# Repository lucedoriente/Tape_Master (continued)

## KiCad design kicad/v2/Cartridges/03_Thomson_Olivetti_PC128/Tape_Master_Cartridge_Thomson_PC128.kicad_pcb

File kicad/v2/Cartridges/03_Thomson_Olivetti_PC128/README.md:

# Tape Master v2 — Expansion Cartridge #03
## Thomson MO5 / TO7 / MO6 / TO8 / TO9 & Olivetti Prodest PC 128 Interface

---

### 1. Overview & Supported Systems
This hardware cartridge provides full bidirectional cassette emulation, high-speed acquisition, motor control sensing, and analog soundtrack digitization for the entire family of Thomson 8-bit computers and their international counterparts:
- **Thomson MO Series**: MO5, MO5E, MO5NR, MO6.
- **Thomson TO Series**: TO7, TO7/70, TO8, TO8D, TO9, TO9+.
- **Olivetti Prodest PC 128**: Licensed Italian rebadged version of the Thomson MO6.

The cartridge features:
1. **Universal 40-Pin Right-Angle Bus (`J1`)**: Perfectly coplanar to the Tape Master Mainboard.
2. **Standard 5-Pin DIN 180° Female Socket (`J2`)**: Compatible with original Thomson LEP (*Lecteur Enregistreur de Programmes*) DIN cables.
3. **Bench Test Header (`J3`)**: 6-pin 2.54 mm header in parallel with detailed silkscreen pinout labels for easy logic analyzer, oscilloscope, and bench testing.
4. **Smart Auto-ID EEPROM (`U1`)**: 24C02 on I2C bus identifying Cartridge ID `#03`.
5. **Bidirectional Signal Conditioning**:
   - `READ` (Cassette In to Computer): Buffered with 74HCT06 open-collector inverter stage with 4.7kΩ pull-up for sharp 5V TTL rise/fall times.
   - `WRITE` (Cassette Out from Computer): Scaled via 2.2kΩ / 3.3kΩ voltage divider and clamped to +3.3V/GND via high-speed Schottky diode BAT54S (`D1`).
   - `REM` (Motor Remote Control): Pull-up to +5V (10kΩ) and level scaled/clamped via BAT54S (`D2`) to feed RP2040 `MOTOR_SENSE`.
   - `AUDIO` (Soundtrack / Secondary channel): AC-coupled via 4.7µF capacitor `C3` into the auxiliary analog digitizer `AUDIO_RAW_L`.
6. **ESD TVS Array (`D3`)**: USBLC6-2SC6 protecting all externally exposed lines against electrostatic discharge.

---

### 2. Connector Pinouts

#### DIN 5-Pin 180° Female Receptacle (`J2`)
Standard DIN 41524 / IEC 60130-9 socket:

| Pin | Net Name | Function | Direction | Electrical Standard |
| :---: | :---: | :--- | :--- | :--- |
| **1** | `THOMSON_REM` | Motor Remote Control | Host $\rightarrow$ Tape Master | Open-Collector / Relay control |
| **2** | `GND` | Ground & Shield reference | Common Power Reference | 0V |
| **3** | `THOMSON_AUDIO`| Analog Audio Channel | Tape Master $\rightarrow$ Host | Analog Audio ($~1\text{V}_{pp}$) |
| **4** | `THOMSON_READ` | Cassette Data In (EAR) | Tape Master $\rightarrow$ Host | 5V TTL Digital Pulses |
| **5** | `THOMSON_WRITE`| Cassette Data Out (MIC)| Host $\rightarrow$ Tape Master | 5V TTL Digital Square Waves |

#### Bench Test Pin-Header (`J3`)
6-pin 2.54 mm right-angle pin-header:

| Pin | Net Name | Description |
| :---: | :---: | :--- |
| **1** | `GND` | Ground reference |
| **2** | `+5V` | Tape Master System +5V Supply |
| **3** | `THOMSON_REM` | Motor Remote Control Sense line |
| **4** | `THOMSON_AUDIO`| Analog Audio soundtrack ingest |
| **5** | `THOMSON_READ` | Buffered 5V Cassette Data In to Host |
| **6** | `THOMSON_WRITE`| Scaled Cassette Data Out from Host |

---

### 3. Production Deliverables Summary

| Artifact | File Name | Description |
| :--- | :--- | :--- |
| **Schematic (PDF)** | `Tape_Master_Cartridge_Thomson_PC128.pdf` | Complete single-sheet schematic with standard page settings |
| **Schematic (SVG)** | `Tape_Master_Cartridge_Thomson_PC128_Sch.svg` | Vector schematic graphic |
| **3D CAD Model (STEP)**| `Tape_Master_Cartridge_Thomson_PC128.step` | Full 3D solid mechanical model |
| **PCB Layout (Top PDF)**| `Tape_Master_Cartridge_Thomson_PC128_Top.pdf` | Vector drawing of Top Copper, Silk, Mask & Edge.Cuts |
| **PCB Layout (Bottom PDF)**| `Tape_Master_Cartridge_Thomson_PC128_Bottom.pdf` | Vector drawing of Bottom Copper, Silk, Mask & Edge.Cuts |
| **PCB Layout (Top SVG)**| `Tape_Master_Cartridge_Thomson_PC128_Top.svg` | Vector layout graphic |
| **Gerber & Drill Files** | `gerbers/` (26 files) | Standard RS-274X Gerbers and Excellon drill files |
| **ERC Report** | `Tape_Master_Cartridge_Thomson_PC128-erc.rpt` | **0 Violations / 0 Warnings** |
| **DRC Report** | `Tape_Master_Cartridge_Thomson_PC128-drc.rpt` | **0 Violations / 0 Unconnected / 0 Parity Issues** |

---

### 4. Verification & Validation Gate
- **KiCad 9.0 CLI ERC**: Passed with **0 errors, 0 warnings**.
- **KiCad 9.0 CLI DRC**: Passed with **0 violations, 0 unconnected items, 0 schematic parity issues**.
- **Compliance Rules**:
  - Mechanical profile $74.00\text{ mm} \times 55.00\text{ mm}$ with $6.00\text{ mm} \times 8.00\text{ mm}$ retention cutouts on `Edge.Cuts`.
  - Zero redundant activity LEDs on cartridge; full UI diagnostics central on Daughterboard.
  - Cartouche with Alessio Iodice, CC BY-NC-SA 4.0 license, and `© 2026 by Alessio Iodice` silkscreen copyright.

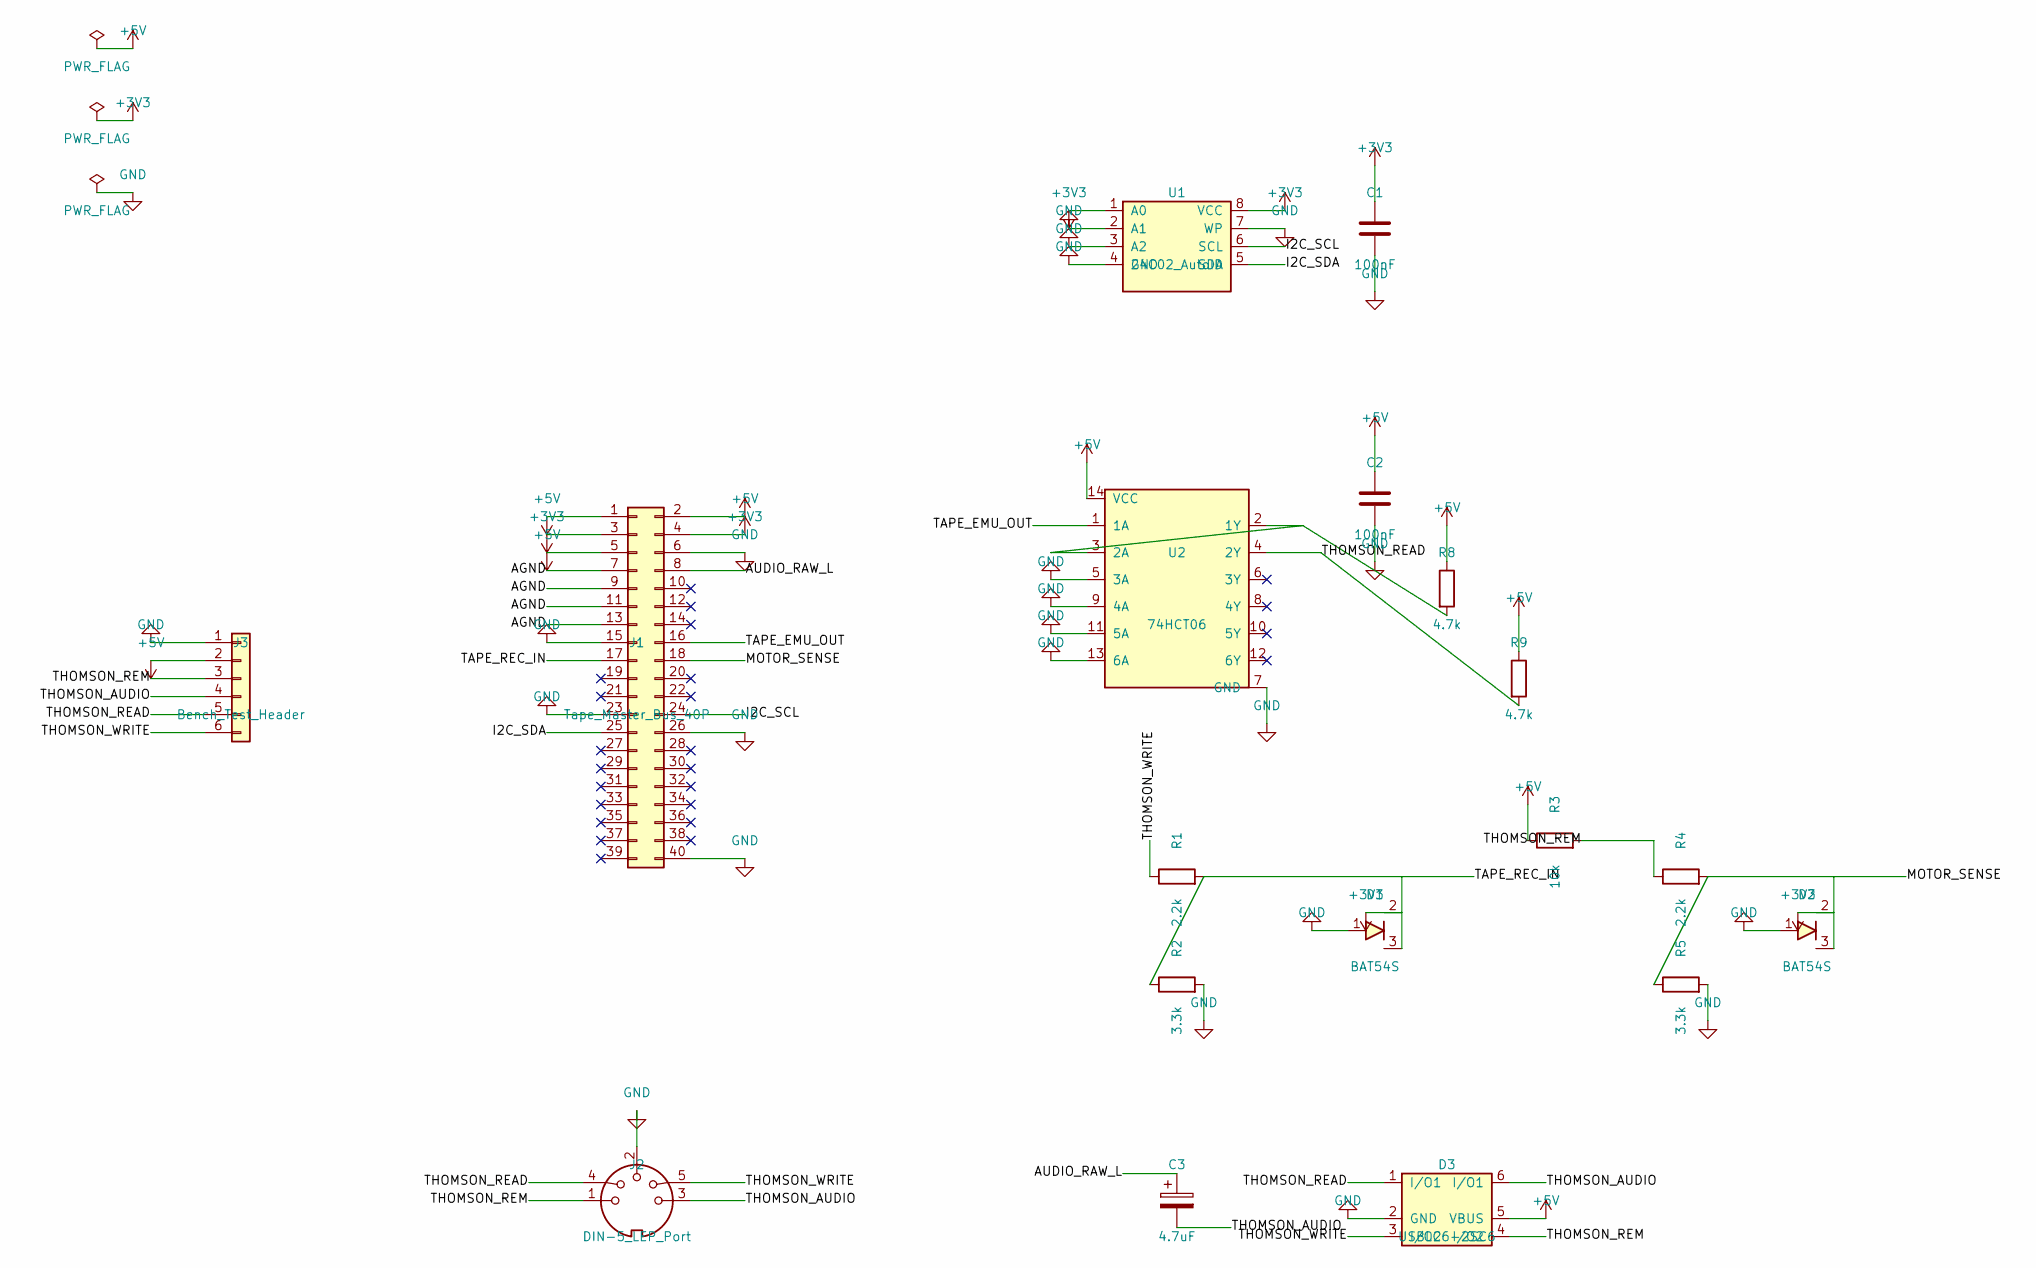
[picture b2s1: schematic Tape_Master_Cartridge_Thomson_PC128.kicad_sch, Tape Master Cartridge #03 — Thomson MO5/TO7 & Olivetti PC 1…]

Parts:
C1, C2: 100nF; C_0805_2012Metric
C3: 4.7uF; CP_Elec_5x5.4
D1, D2: BAT54S; SOT-23
D3: USBLC6-2SC6; SOT-23-6
J1: Tape_Master_Bus_40P; PinSocket_2x20_P2.54mm_Horizontal_Cartridge
J2: DIN-5_LEP_Port; DIN-5_180_Horizontal_CUI_SDS-50J
J3: Bench_Test_Header; PinHeader_1x06_P2.54mm_Vertical
R1, R4: 2.2k; R_0805_2012Metric
R2, R5: 3.3k; R_0805_2012Metric
R3: 10k; R_0805_2012Metric
R8, R9: 4.7k; R_0805_2012Metric
U1: 24C02_AutoID; SOIC-8_3.9x4.9mm_P1.27mm
U2: 74HCT06; SOIC-14_3.9x8.7mm_P1.27mm

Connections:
+3V3: C1.1, D1.2 (C2), D2.2 (C2), J1.3, J1.4, U1.1 (A0), U1.8 (VCC)
+5V: C2.1, D3.5 (VBUS), J1.1, J1.2, J1.5, J3.2, R3.1, R8.1, R9.1, U2.14 (VCC)
/AGND: J1.7, J1.9, J1.11, J1.13
/AUDIO_RAW_L: C3.1, J1.8
/I2C_SCL: J1.24, U1.6 (SCL)
/I2C_SDA: J1.25, U1.5 (SDA)
/MOTOR_SENSE: D2.3 (C1A2), J1.18, R4.2, R5.1
/TAPE_EMU_OUT: J1.16, U2.1 (1A)
/TAPE_REC_IN: D1.3 (C1A2), J1.17, R1.2, R2.1
/THOMSON_AUDIO: C3.2, D3.6 (I/O1), J2.3, J3.4
/THOMSON_READ: D3.1 (I/O1), J2.4, J3.5, R9.2, U2.4 (2Y)
/THOMSON_REM: D3.4 (I/O2), J2.1, J3.3, R3.2, R4.1
/THOMSON_WRITE: D3.3 (I/O2), J2.5, J3.6, R1.1
GND: C1.2, C2.2, D1.1 (A1), D2.1 (A1), D3.2 (GND), J1.6, J1.15, J1.23, J1.26, J1.40, J2.2, J3.1, R2.2, R5.2, U1.2 (A1), U1.3 (A2), U1.4 (GND), U1.7 (WP), U2.5 (3A), U2.7 (GND), U2.9 (4A), U2.11 (5A), U2.13 (6A)
unnamed: R8.2, U2.2 (1Y), U2.3 (2A)

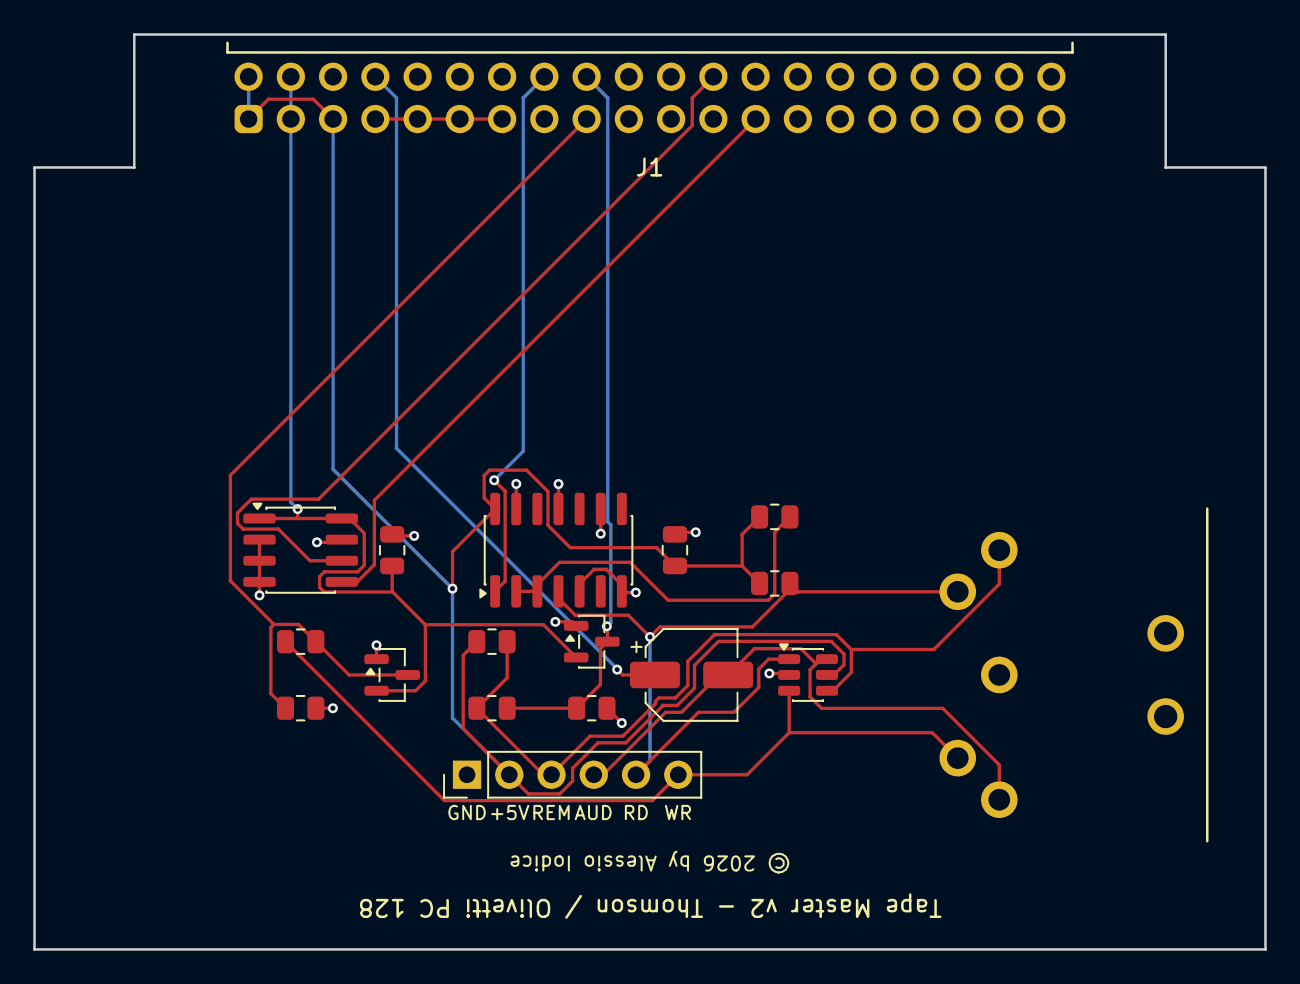
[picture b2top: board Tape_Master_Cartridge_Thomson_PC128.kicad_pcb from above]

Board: 2 copper layers, 74.0 x 55.0 mm, 18 parts (0 on the bottom side), 15 nets.

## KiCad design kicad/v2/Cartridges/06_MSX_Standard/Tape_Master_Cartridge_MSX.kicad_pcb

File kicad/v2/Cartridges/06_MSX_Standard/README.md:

# Tape Master v2 — Cartuccia 06: MSX Standard Tape Interface

| Proprietà | Dettaglio / Valore |
| :--- | :--- |
| **Progetto** | Tape Master Exerciser & Signal Digitizer v2 |
| **Modulo** | Cartuccia Espansione #06 — MSX Standard (`06_MSX_Standard`) |
| **Piattaforme Compatibili** | Standard MSX1, MSX2, MSX2+, MSX Turbo R (Sony HitBit, Philips NMS/VG, Yamaha CX, Panasonic FS, Sanyo, National, Canon, Pioneer, Spectravideo, Casio, etc.) |
| **Periferiche Supportate** | Registratori a cassetta MSX dedicati (Sony SDC-500/600, Philips NMS-1515, Panasonic RQ-8300, etc.), registratori portatili generici via cavo DIN-8 a 3 jack (EAR, MIC, REM), interfacce turbo (CasLink, etc.) |
| **Autore & Hardware Designer** | Alessio Iodice (`alessio67@gmail.com`) |
| **Data di Rilascio** | 2026-11-06 |
| **Revisione** | 2.0 (KiCad 9.0 Nativo) |
| **Licenza** | CC BY-NC-SA 4.0 |
| **Stato Validazione KiCad 9** | **0 Violazioni ERC / 0 Violazioni DRC / 0 Net Non Connesse / 0 Parity Issues** |

---

## 1. Descrizione Architetturale

La **Cartuccia 06: MSX Standard** interfaccia il sistema **Tape Master v2** alla porta a cassetta universale standardizzata per l'intero ecosistema **MSX** (costruttori giapponesi ed europei), adottando il connettore circolare **DIN 8-Pin 270°** (standard MSX e connettore CUI/Same Sky SDS-80J).

### Caratteristiche Elettriche Chiave
1. **Canale Riproduzione Dati (CMTIN - Pin 5 DIN)**:
   - Ingresso del registratore nel computer MSX (modulazione audio FSK: $1200\text{ baud} \rightarrow 1200/2400\text{ Hz}$, oppure $2400\text{ baud} \rightarrow 2400/4800\text{ Hz}$).
   - Pilotaggio ad alta velocità e precisione tramite buffer open-collector **74HCT06** (`U2`) configurato a doppio stadio logico con pull-up da $4.7\text{ k}\Omega$ (`R7`, `R8`) a `+5V`.
   - Rete di attenuazione, disaccoppiamento AC e calibrazione del livello audio verso il circuito comparatore/amplificatore interno dell'MSX: resistenza serie $1\text{ k}\Omega$ (`R9`), condensatore di disaccoppiamento AC $4.7\ \mu\text{F}$ (`C3`) e resistenza di carico $10\text{ k}\Omega$ (`R10`) a massa.
2. **Canale Registrazione Dati (CMTOUT - Pin 4 DIN)**:
   - Uscita audio analogica generata dal computer MSX durante il comando `CSAVE` o `SAVE "CAS:"` (ampiezza tipica $\approx 1 \dots 2\text{ V}_{pp}$ centrata a $0\text{ V}$ o livello logico con componente DC).
   - Traslazione di livello verso il bus a 3.3V tramite partitore resistivo ($R_1 = 2.2\text{ k}\Omega$, $R_2 = 3.3\text{ k}\Omega$) protetto da clamp a doppio diodo Schottky ultra-veloce **BAT54S** (`D1`) verso `+3.3V` e `GND`, collegato alla linea `TAPE_REC_IN` del microcontrollore Tape Master.
   - Derivazione audio analogica AC con condensatore di blocco da $4.7\ \mu\text{F}$ (`C4`), filtro RC passa-basso anti-aliasing ($R_{11} = 1\text{ k}\Omega$, $C_5 = 10\text{ nF}$) e resistenza di carico $10\text{ k}\Omega$ (`R12`) collegata al canale ADC `AUDIO_RAW_L` per il monitoraggio continuo sul display OLED e sul VU-meter a 10 segmenti del pannello frontale.
3. **Controllo e Monitoraggio Motore (REMOTE - Pin 6 REM+ & Pin 7 REM-)**:
   - Nello standard MSX, il controllo motore è affidato a un relè interno pilotato dal chip PPI (8255, porta C, bit 4). I due terminali del relè sono attestati su Pin 6 (`REM+`) e Pin 7 (`REM-`).
   - **Rilevamento Chiamata Motore (`MOTOR_SENSE`)**: Pin 6 (`REM+`) è vincolato a massa tramite jumper/resistore da $0\ \Omega$ (`R15`). Pin 7 (`REM-`) è polarizzato a +5V con pull-up da $10\text{ k}\Omega$ (`R3`) e collegato al partitore resistivo ($R_4 = 2.2\text{ k}\Omega$, $R_5 = 3.3\text{ k}\Omega$) con clamp Schottky **BAT54S** (`D2`) verso `MOTOR_SENSE`. Quando il computer MSX attiva il comando `MOTOR ON`, il relè interno chiude il circuito tra REM+ e REM-, portando Pin 7 a massa e segnalando al microcontrollore lo stato attivo a livello basso ($0\text{ V}$).
   - **Pilotaggio Motore Attivo Registratore Esterno (`MOTOR_CTRL`)**: N-MOSFET di commutazione **2N7002** (`Q1`) collegato tra Pin 7 e Pin 6 (massa), con gate pilotato da `MOTOR_CTRL` tramite resistenza di gate da $100\ \Omega$ (`R13`) e resistenza di pull-down da $100\text{ k}\Omega$ (`R14`). Consente al Tape Master di azionare autonomamente il motore di un registratore MSX reale durante le procedure di taratura, acquisizione automatizzata o test di durata.
4. **Protezione ESD / Transitori (TVS Diode Array)**:
   - Array di diodi TVS ultra-rapido a bassa capacità **USBLC6-4SC6** (`U3`, package SOT-23-6L) a protezione diretta di tutte le linee esposte verso l'esterno (`CMTOUT`, `CMTIN`, `REM+`, `REM-`).
5. **Smart Plug & Play (Auto-ID Cartridge)**:
   - EEPROM seriale I2C **24C02** (`U1`) configurata all'indirizzo `0x50` (`A0=0, A1=0, A2=0`), contenente il descrittore binario univoco della cartuccia MSX Standard (Vendor ID, Board Revision, pin mapping e baud rate predefiniti).
   - Pin 26 del connettore bus principale `CART_DETECT_N` collegato permanentemente a massa per rilevamento hardware istantaneo all'inserimento.

---

## 2. Centralizzazione Diagnostica sul Front Panel (Daughterboard)

In ottemperanza alle regole di progetto `tape-master-rules.md`, tutti gli indicatori di stato e la diagnostica visiva sono centralizzati sul pannello frontale (`Tape_Master_UI_Panel`), evitando LED duplicati sulla cartuccia che risulterebbero coperti a banco dall'innesto del cavo DIN e dei connettori.

I 5 LED diagnostici standardizzati sul pannello frontale riflettono il funzionamento della cartuccia MSX Standard:

| Riferimento UI | Colore | Serigrafia Standard | Segnale Mappato per MSX Standard | Funzione Operativa |
| :---: | :---: | :---: | :--- | :--- |
| **D2** | Verde | **`PLAY`** | `CMTIN` (Pin 5 DIN) | Trasmissione dati verso il computer MSX (emulazione nastro / riproduzione file CAS / WAV) |
| **D3** | Rosso | **`REC`** | `CMTOUT` (Pin 4 DIN) | Ricezione dati dal computer MSX verso il Tape Master (salvataggio dump da `CSAVE`) |
| **D4** | Giallo | **`MOTOR`** | `REM-` / `REM+` (Pin 6/7 DIN) | Relè motore chiuso dal comando `MOTOR ON` dell'MSX o forzatura motore attiva |
| **D5** | Blu | **`SIGNAL`** | Rilevamento portante FSK | Leader tone $1200/2400\text{ Hz}$ o modulazione dati MSX rilevata |
| **D6** | Verde | **`PWR`** | Alimentazione Tape Master | Alimentazione principale di sistema attiva (+5V / +3.3V) e MCU operativo |
| **D10..D19** | 8V/1G/1R | **`AZIMUTH / VU-METER`** | Livello picco ADC `AUDIO_RAW_L` | Barra VU-meter per regolazione azimut / ampiezza segnale audio analogico `CMTOUT` |

---

## 3. Doppia Connettività Esterna

La cartuccia adotta l'architettura a **doppia porta**:
1. **`J2` — Presa DIN 8-Pin 270° Femmina (CUI SDS-80J)**: Connettore circolare orizzontale a montaggio su circuito stampato per il cavo originale MSX a 8 poli.
2. **`J3` — Pin-Header Maschio Breakout 1x08 passo 2.54 mm**: Pin-header orizzontale serigrafato posto sul bordo inferiore del PCB, progettato per collegamenti rapidi a banco, oscilloscopio, analizzatore di stati logici e cavi volanti.

### Piedinatura Connettori (`J2` e `J3`)

| Pin # J3 | Pin # J2 (DIN-8) | Serigrafia J3 | Segnale | Direzione Elettrica | Descrizione Tecnica MSX |
| :---: | :---: | :--- | :--- | :---: | :--- |
| **1** | **1, 2, 3, 8** | `GND` | `GND` | Riferimento | Massa comune di segnale e schermo del cavo |
| **2** | — | `+5V` | `+5V` | Potenza | Tensione alimentazione Tape Master per test a banco |
| **3** | **1, 2, 3, 8** | `GND` | `GND` | Riferimento | Massa di ritorno addizionale |
| **4** | **4** | `OUT` | `MSX_CMTOUT` | Dal computer (Output) | Uscita registratore MSX (Cassette Data Out dal computer al nastro) |
| **5** | **5** | `IN` | `MSX_CMTIN` | Al computer (Input) | Ingresso registratore MSX (Cassette Data In dal nastro al computer) |
| **6** | **6** | `R+` | `MSX_REM_PLUS` | Contatto relè MSX | Terminale positivo relè motore (a massa sulla scheda) |
| **7** | **7** | `R-` | `MSX_REM_MINUS` | Contatto relè MSX | Terminale negativo relè motore (pull-up + sense + switch MOSFET) |
| **8** | **1, 2, 3, 8** | `GND` | `GND` | Riferimento | Massa logica e riferimento schermatura |

---

## 4. Specifiche Meccaniche e Bordo Scheda

- **Dimensioni Form Factor**: $74.00\text{ mm} \times 55.00\text{ mm}$ conforme allo standard unificato delle Cartucce Tape Master v2.
- **Intagli Meccanici di Blocco**: Due intagli precisi su layer `Edge.Cuts` ($6.0\text{ mm} \times 8.0\text{ mm}$) per l'alloggiamento delle leve di ritenuta del connettore `J1` della Mainboard.
- **Complanarità e Disposizione**:
  - Connettore bus maschio ad angolo retto sulla Mainboard e connettore femmina ad angolo retto sulla Cartuccia (`J1`) garantiscono una perfetta complanarità tra le due schede.
  - La cartuccia estende la Mainboard orizzontalmente all'indietro, mantenendo i cavi e il connettore DIN-8 lontano dal campo visivo dell'operatore e dai comandi frontali dell'UI Panel.
- **Serigrafia di Copyright**: Prescritta e presente su `F.Silkscreen` con la dicitura ufficiale `© 2026 by Alessio Iodice`.

---

## 5. File di Rilascio e Produzione

- Schema Elettrico KiCad: `Tape_Master_Cartridge_MSX.kicad_sch`
- Layout PCB KiCad: `Tape_Master_Cartridge_MSX.kicad_pcb`
- Modello 3D Meccanico Solido PCB Assemblato: `Tape_Master_Cartridge_MSX.step`
- Schema Elettrico Vettoriale: `Tape_Master_Cartridge_MSX.pdf` e `Tape_Master_Cartridge_MSX_Sch.svg`
- Disegno PCB Top Layer: `Tape_Master_Cartridge_MSX_Top.pdf` e `Tape_Master_Cartridge_MSX_Top.svg`
- Disegno PCB Bottom Layer: `Tape_Master_Cartridge_MSX_Bottom.pdf`
- Pacchetto Gerbers & Drills Produzione: cartella `gerbers/`
- Report di Validazione KiCad 9:
  - ERC: `Tape_Master_Cartridge_MSX-erc.rpt` (**0 errori / 0 warning**)
  - DRC: `Tape_Master_Cartridge_MSX-drc.rpt` (**0 violazioni / 0 unconnected / 0 parity**)

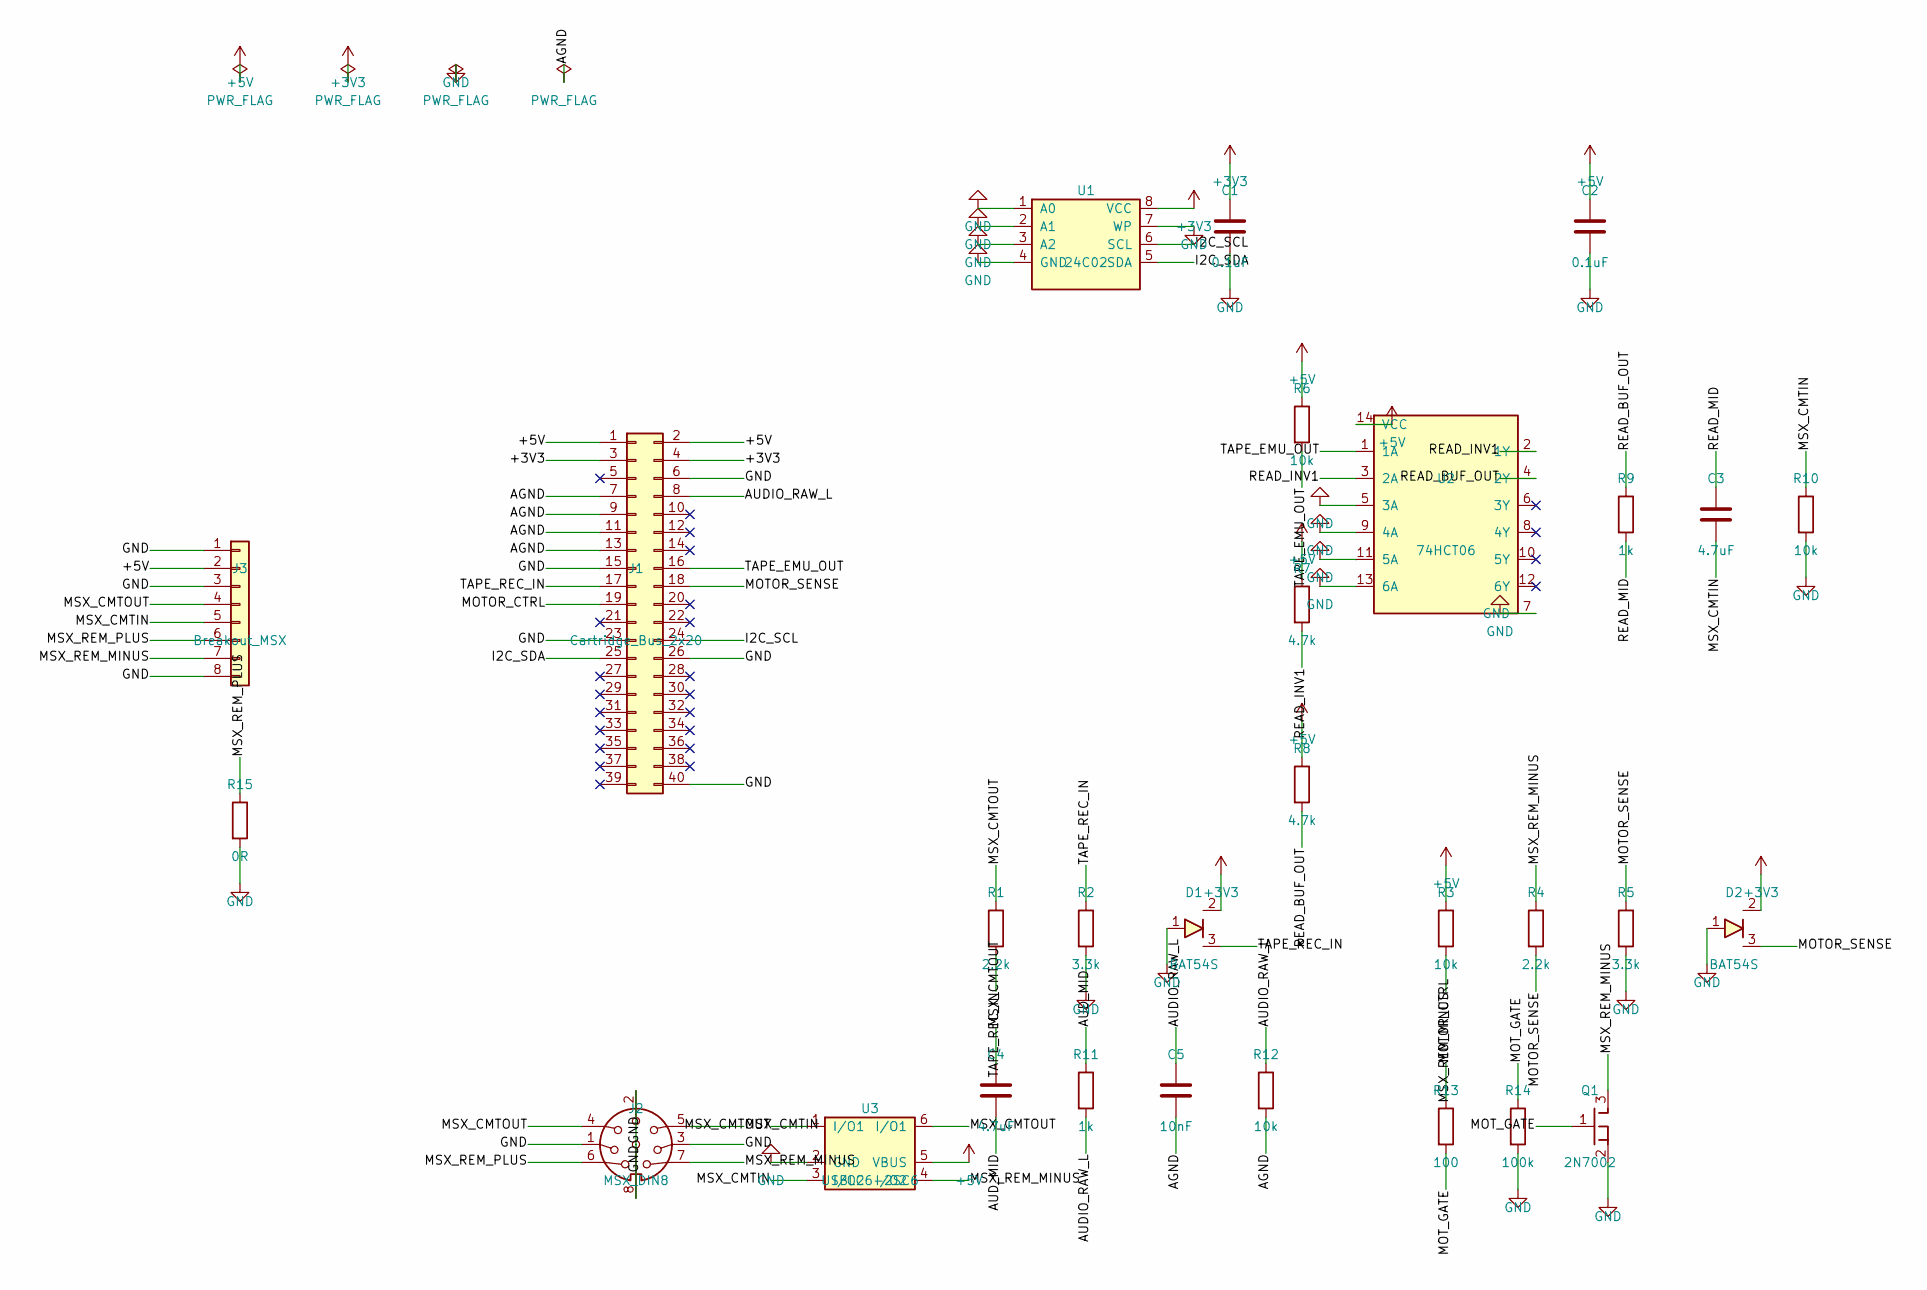
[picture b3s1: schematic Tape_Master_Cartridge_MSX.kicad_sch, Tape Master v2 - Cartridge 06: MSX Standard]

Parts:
C1, C2: 0.1uF; C_0805_2012Metric
C3, C4: 4.7uF; C_0805_2012Metric
C5: 10nF; C_0805_2012Metric
D1, D2: BAT54S; SOT-23
J1: Cartridge_Bus_2x20; PinSocket_2x20_P2.54mm_Horizontal_Cartridge
J2: MSX_DIN8; DIN-8_270_Horizontal_CUI_SDS-80J
J3: Breakout_MSX; PinHeader_1x08_P2.54mm_Vertical
Q1: 2N7002; SOT-23
R1, R4: 2.2k; R_0805_2012Metric
R2, R5: 3.3k; R_0805_2012Metric
R3, R6, R10, R12: 10k; R_0805_2012Metric
R7, R8: 4.7k; R_0805_2012Metric
R9, R11: 1k; R_0805_2012Metric
R13: 100; R_0805_2012Metric
R14: 100k; R_0805_2012Metric
R15: 0R; R_0805_2012Metric
U1: 24C02; SOIC-8_3.9x4.9mm_P1.27mm
U2: 74HCT06; SOIC-14_3.9x8.7mm_P1.27mm
U3: USBLC6-2SC6; SOT-23-6

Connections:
+3V3: C1.1, D1.2 (C2), D2.2 (C2), J1.3, J1.4, U1.8 (VCC)
+5V: C2.1, J1.1, J1.2, J3.2, R3.1, R6.1, R7.1, R8.1, U2.14 (VCC), U3.5 (VBUS)
/AGND: C5.2, J1.7, J1.9, J1.11, J1.13, R12.2
/AUDIO_RAW_L: C5.1, J1.8, R11.2, R12.1
/AUD_MID: C4.2, R11.1
/I2C_SCL: J1.24, U1.6 (SCL)
/I2C_SDA: J1.25, U1.5 (SDA)
/MOTOR_CTRL: J1.19, R13.1
/MOTOR_SENSE: D2.3 (C1A2), J1.18, R4.2, R5.1
/MOT_GATE: Q1.1 (G), R13.2, R14.1
/MSX_CMTIN: C3.2, J2.5, J3.5, R10.1, U3.3 (I/O2)
/MSX_CMTOUT: C4.1, J2.4, J3.4, R1.1, U3.1 (I/O1), U3.6 (I/O1)
/MSX_REM_MINUS: J2.7, J3.7, Q1.3 (D), R3.2, R4.1, U3.4 (I/O2)
/MSX_REM_PLUS: J2.6, J3.6, R15.1
/READ_BUF_OUT: R8.2, R9.1, U2.4 (2Y)
/READ_INV1: R7.2, U2.2 (1Y), U2.3 (2A)
/READ_MID: C3.1, R9.2
/TAPE_EMU_OUT: J1.16, R6.2, U2.1 (1A)
/TAPE_REC_IN: D1.3 (C1A2), J1.17, R1.2, R2.1
GND: C1.2, C2.2, D1.1 (A1), D2.1 (A1), J1.6, J1.15, J1.23, J1.26, J1.40, J2.1, J2.2, J2.3, J2.8, J3.1, J3.3, J3.8, Q1.2 (S), R2.2, R5.2, R10.2, R14.2, R15.2, U1.1 (A0), U1.2 (A1), U1.3 (A2), U1.4 (GND), U1.7 (WP), U2.5 (3A), U2.7 (GND), U2.9 (4A), U2.11 (5A), U2.13 (6A), U3.2 (GND)

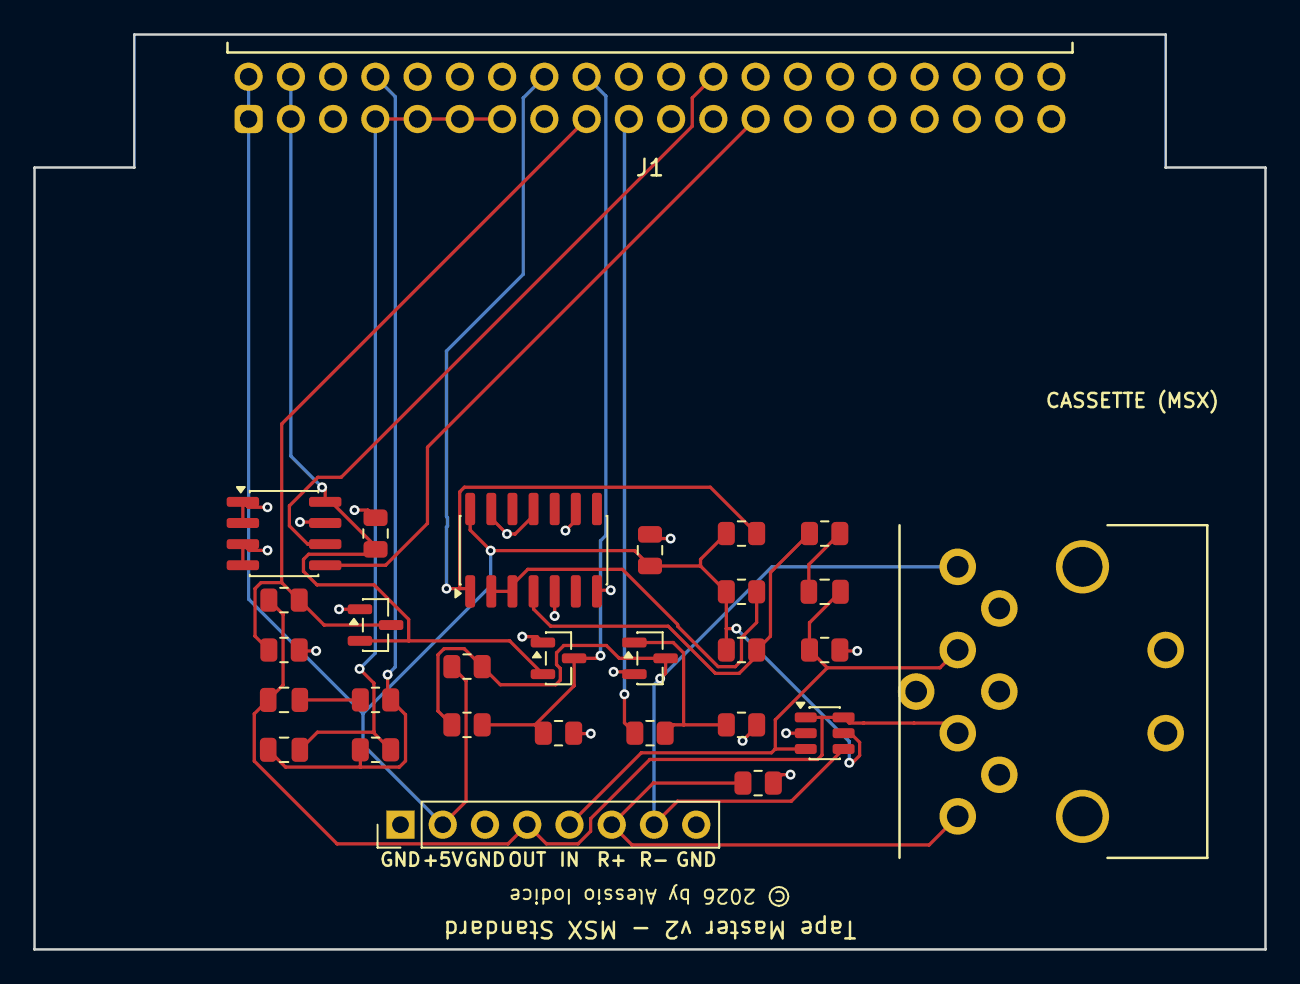
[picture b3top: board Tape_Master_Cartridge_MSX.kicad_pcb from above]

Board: 2 copper layers, 74.0 x 55.0 mm, 29 parts (0 on the bottom side), 20 nets.
